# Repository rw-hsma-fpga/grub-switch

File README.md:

# THE GRUB SWITCH&nbsp;&nbsp;   

#### See [*quickstart.pdf*](./quickstart.pdf) for the fastest way to your custom boot configuration.

#### (c) 2019-2023 Ruediger Willenberg

This project enables PC users to select the OS to be booted by *GRUB* through hardware.
It has three independently usable components:

### 1. Configuration scripts ###

A suite of *bash* scripts in **1_config_scripts**, all controlled by one easy-to-use text UI, that provide the following capabilities:
* parse the **grub.cfg** file for all menu entries that represent OS boot options
* enable the user to pick menu entries and order them with numbers (1..15)
* generate *GRUB* script files that make a specific menu entry the default choice; these files can be put on separate USB flash drives; plugging one in will represent that choice of OS to be booted
* enhance the existing **grub.cfg** - in a non-destructive way that survives kernel updates - to look for a boot choice script on a plugged-in drive
* install a list of file hashes in *GRUB* so that only the generated files will be executed

When using several USB flash drives for the boot choices (small, old ones will do), no further hardware is necessary.

*GRUB* does not need to be patched, rebuilt or reinstalled. The employed extension of **grub.cfg** is robust against unavailable or malformed data. Any unexpected choices or scripts will be ignored. You can always get to the regular *GRUB* boot menu.

### 2. USB device firmware

The **2_usb_device** directory holds firmware source code for *Microchip/Atmel ATmega32U4* MCUs that can act as USB devices. It has build support and pre-built firmware images for common maker boards like *Teensy 2.0*, *Arduino Micro*, *Adafruit ItsyBitsy* and *Sparkfun Pro Micro*. Other boards with the ATmega32u4 can be easily added.

A board with the firmware installed will register as a regular USB flash drive when plugged in and provide one of the generated files for the regular flash drives; however, you can control which file (i.e. which boot choice) is picked through pins on the board.

The firmware does NOT need to be rebuilt to change the boot configuration; a new boot configuration can just be written to the USB drive. With a switch or jumper, *write-protect* can be activated.

Boards can be connected to common *rotary*, *toggle* or *binary-encoding* switches to realize boot choice.

### 3. Custom USB Hardware 

For easier panel and case mounting (and for fun), we designed our own PCB for *ATmega32U4* or *ATmega16U4* chips. *EAGLE* and *Gerber* files and all other required information can be found in **3_custom_hardware**. It features:

* Solder pads for common *1-of-12-rotary encoder* and *on/off/on-toggle* switches with front panel mounting threads; no soldering cables required.
* Supports USB connection both by *Mini-B*-plug or directly by internal ribbon cable to motherboard USB pinheaders.
* Firmware easily re-programmable by pushing a button; works with factory *ATmega32U4* chips, no custom bootloader needs to be installed.
* Switch- or jumper-controlled *write-protect*
* Can be used with self-written firmware for other purposes, like any commercial board; provides up to 13 I/O-pins with 5V logic.

Obviously this requires soldering skills and is likely not the cheapest hardware option, especially because you have to order your own PCB. But it's fun!

### NEW: Miscellaneous contributions
In directory *4_misc*, you can find community contributions like case designs and wiring diagrams that could be helpful with GRUB Switch building, mounting, etc.

---

### Acknowledgements 

Many thanks to Seriosha Remmlinger, Volker Wunsch and Andreas Flachsbarth for helpful feedback and suggestions and to Christoph Dehmer for examining an alternative approach (GRUB menu control by USB HID keyboard).

Thank you to Pina Merkert from Germany's biggest computer magazine [*c't*](https://www.heise.de/ct) for helping me write and publish an article about this, and for her cool contributions in *4_misc*.

Stephen Holdaway has a very cool [*Hackaday* project](https://hackaday.io/project/179539-hardware-boot-selection-switch) doing something similar with an *STM32* controller. He's built a very neat way to define the FAT file structure in his C code.

We are grateful to [*pid.codes*](https://pid.codes/) for providing our firmware with a unique USB ID *(VID 1209 / PID 2015)*.

Thank you to the GNU GRUB developers and maintainers for all their hard work.

---

#### See [*quickstart.pdf*](./quickstart.pdf) for the fastest way to your custom boot configuration.

The [*documentation*](./documentation/) directory holds more detailed information.

Send any questions or suggestions to [*grubswitch@gmail.com*](mailto:grubswitch@gmail.com). Please be patient. I have a life.

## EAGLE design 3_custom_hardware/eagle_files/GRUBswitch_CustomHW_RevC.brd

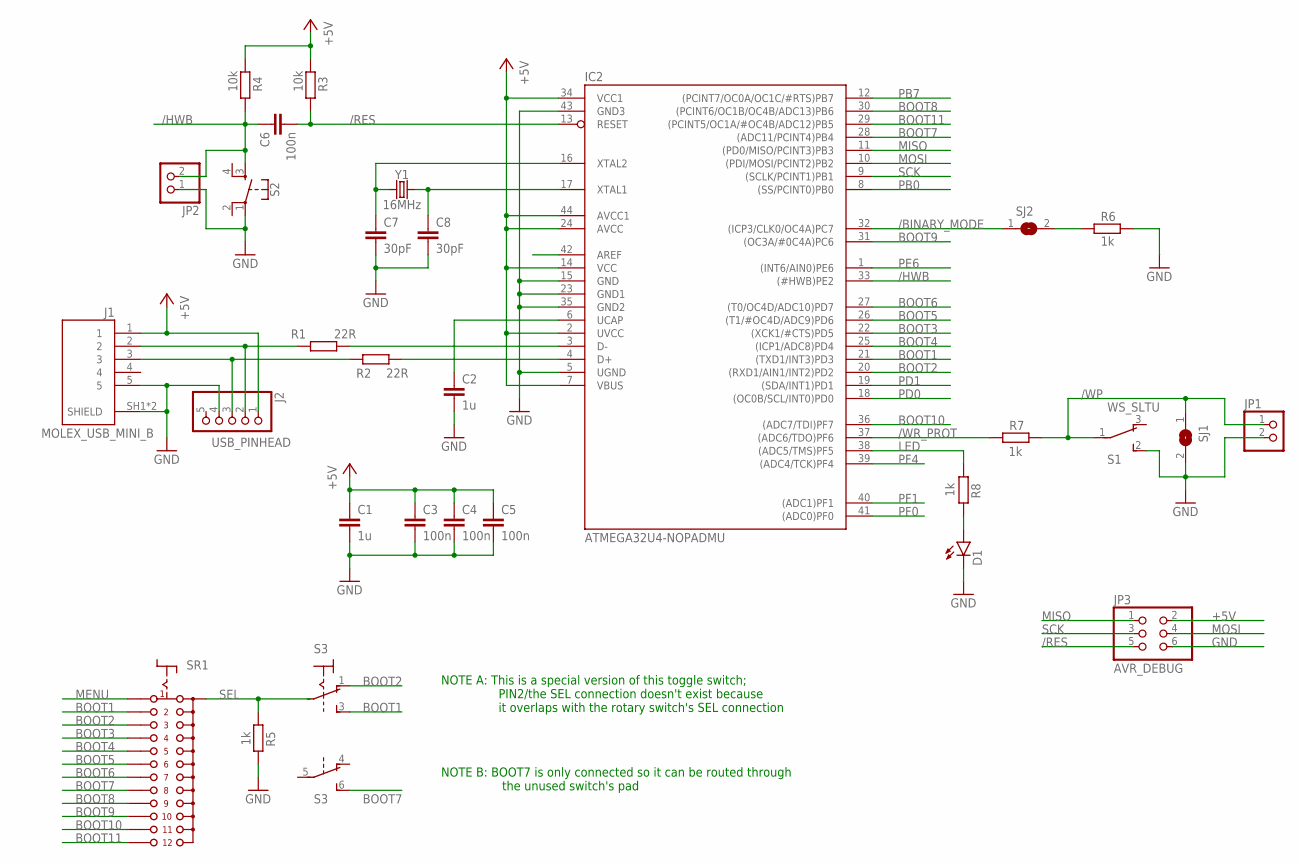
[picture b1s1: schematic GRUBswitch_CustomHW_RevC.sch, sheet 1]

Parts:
C1, C2: 1u; C0805
C3, C4, C5, C6: 100n; C0805
C7, C8: 30pF; C0805
D1: LEDCHIPLED_0805; CHIPLED_0805
IC2: ATMEGA32U4-NOPADMU; QFN-44-NOPAD
J1: MOLEX_USB_MINI_B; MOLEX_502237-0517
J2: USB_PINHEAD; 1X05
JP1, JP2: PINHD-1X2; 1X02
JP3: AVR_DEBUG; 2X03_SMD
R1, R2: 22R; R0805
R3, R4: 10k; R0805
R5, R6, R7, R8: 1k; R0805
S1: WS_SLTU
S2: MOMENTARY-SWITCH-SPST-2-SMD-4.5MM; TACTILE_SWITCH_SMD_4.5MM
S3: M9040P2
SJ1, SJ2: SJ
SR1: CK101X12+
Y1: 16MHz; CRYSTAL-SMD-5X3.2-2PAD

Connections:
+5V: C1.1, C3.1, C4.1, C5.1, IC2.2 (UVCC), IC2.7 (VBUS), IC2.14 (VCC), IC2.24 (AVCC), IC2.34 (VCC1), IC2.44 (AVCC1), J1.1, J2.1, JP3.2, R3.2, R4.2; also elsewhere on the board
/BINARY_MODE: IC2.32 ((ICP3/CLK0/OC4A)PC7), SJ2.1; also elsewhere on the board
/BM: R6.1, SJ2.2
/HWB: C6.1, IC2.33 ((#HWB)PE2), JP2.2, R4.1, S2.3; also elsewhere on the board
/RES: C6.2, IC2.13 (RESET), JP3.5, R3.1; also elsewhere on the board
/WP: JP1.1, R7.1, S1.1, SJ1.1
/WR_PROT: IC2.37 ((ADC6/TDO)PF6), R7.2; also elsewhere on the board
AREF: IC2.42 (AREF); also elsewhere on the board
BOOT1: IC2.21 ((TXD1/INT3)PD3), S3.3 (S), SR1.2; also elsewhere on the board
BOOT2: IC2.20 ((RXD1/AIN1/INT2)PD2), S3.1 (O), SR1.3; also elsewhere on the board
BOOT3: IC2.22 ((XCK1/#CTS)PD5), SR1.4; also elsewhere on the board
BOOT4: IC2.25 ((ICP1/ADC8)PD4), SR1.5; also elsewhere on the board
BOOT5: IC2.26 ((T1/#OC4D/ADC9)PD6), SR1.6; also elsewhere on the board
BOOT6: IC2.27 ((T0/OC4D/ADC10)PD7), SR1.7; also elsewhere on the board
BOOT7: IC2.28 ((ADC11/PCINT4)PB4), S3.6 (S), SR1.8; also elsewhere on the board
BOOT8: IC2.30 ((PCINT6/OC1B/OC4B/ADC13)PB6), SR1.9; also elsewhere on the board
BOOT9: IC2.31 ((OC3A/#0C4A)PC6), SR1.10; also elsewhere on the board
BOOT10: IC2.36 ((ADC7/TDI)PF7), SR1.11; also elsewhere on the board
BOOT11: IC2.29 ((PCINT5/OC1A/#OC4B/ADC12)PB5), SR1.12; also elsewhere on the board
D+: J1.3, J2.3, R2.1
D-: J1.2, J2.2, R1.1
GND: C1.2, C2.2, C3.2, C4.2, C5.2, C7.2, C8.2, D1.C, IC2.5 (UGND), IC2.15 (GND), IC2.23 (GND1), IC2.35 (GND2), IC2.43 (GND3), J1.5, J1.SH1 (SHIELD), J1.SH2 (SHIELD), J2.4, JP1.2, JP2.1, JP3.6, R5.2, R6.2, S1.2 (S), S2.1, SJ1.2; also elsewhere on the board
LED: IC2.38 ((ADC5/TMS)PF5), R8.2; also elsewhere on the board
MENU: SR1.1
MISO: IC2.11 ((PD0/MISO/PCINT3)PB3), JP3.1; also elsewhere on the board
MOSI: IC2.10 ((PDI/MOSI/PCINT2)PB2), JP3.4; also elsewhere on the board
unnamed: D1.A, R8.1
PB0: IC2.8 ((SS/PCINT0)PB0); also elsewhere on the board
PB7: IC2.12 ((PCINT7/OC0A/OC1C/#RTS)PB7); also elsewhere on the board
PD0: IC2.18 ((OC0B/SCL/INT0)PD0); also elsewhere on the board
PD1: IC2.19 ((SDA/INT1)PD1); also elsewhere on the board
PE6: IC2.1 ((INT6/AIN0)PE6); also elsewhere on the board
PF0: IC2.41 ((ADC0)PF0); also elsewhere on the board
PF1: IC2.40 ((ADC1)PF1); also elsewhere on the board
PF4: IC2.39 ((ADC4/TCK)PF4); also elsewhere on the board
R_D+: IC2.4 (D+), R2.2; also elsewhere on the board
R_D-: IC2.3 (D-), R1.2; also elsewhere on the board
SCK: IC2.9 ((SCLK/PCINT1)PB1), JP3.3; also elsewhere on the board
SEL: R5.1, SR1.A
UCAP: C2.1, IC2.6 (UCAP); also elsewhere on the board
XTAL1: C8.1, IC2.17 (XTAL1), Y1.P$2 (2); also elsewhere on the board
XTAL2: C7.1, IC2.16 (XTAL2), Y1.P$1 (1); also elsewhere on the board

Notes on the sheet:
NOTE A: This is a special version of this toggle switch; PIN2/the SEL connection doesn't exist because it overlaps with the rotary switch's SEL connection
NOTE B: BOOT7 is only connected so it can be routed through the unused switch's pad

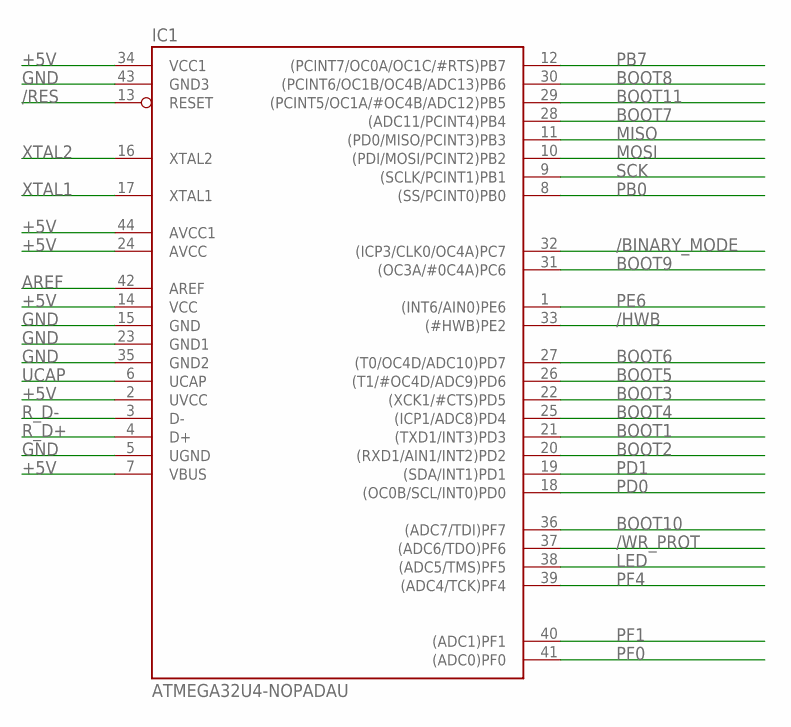
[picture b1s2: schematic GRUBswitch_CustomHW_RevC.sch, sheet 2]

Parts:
IC1: ATMEGA32U4-NOPADAU; TQFP44

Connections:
+5V: IC1.2 (UVCC), IC1.7 (VBUS), IC1.14 (VCC), IC1.24 (AVCC), IC1.34 (VCC1), IC1.44 (AVCC1); also elsewhere on the board
/BINARY_MODE: IC1.32 ((ICP3/CLK0/OC4A)PC7); also elsewhere on the board
/HWB: IC1.33 ((#HWB)PE2); also elsewhere on the board
/RES: IC1.13 (RESET); also elsewhere on the board
/WR_PROT: IC1.37 ((ADC6/TDO)PF6); also elsewhere on the board
AREF: IC1.42 (AREF); also elsewhere on the board
BOOT1: IC1.21 ((TXD1/INT3)PD3); also elsewhere on the board
BOOT2: IC1.20 ((RXD1/AIN1/INT2)PD2); also elsewhere on the board
BOOT3: IC1.22 ((XCK1/#CTS)PD5); also elsewhere on the board
BOOT4: IC1.25 ((ICP1/ADC8)PD4); also elsewhere on the board
BOOT5: IC1.26 ((T1/#OC4D/ADC9)PD6); also elsewhere on the board
BOOT6: IC1.27 ((T0/OC4D/ADC10)PD7); also elsewhere on the board
BOOT7: IC1.28 ((ADC11/PCINT4)PB4); also elsewhere on the board
BOOT8: IC1.30 ((PCINT6/OC1B/OC4B/ADC13)PB6); also elsewhere on the board
BOOT9: IC1.31 ((OC3A/#0C4A)PC6); also elsewhere on the board
BOOT10: IC1.36 ((ADC7/TDI)PF7); also elsewhere on the board
BOOT11: IC1.29 ((PCINT5/OC1A/#OC4B/ADC12)PB5); also elsewhere on the board
GND: IC1.5 (UGND), IC1.15 (GND), IC1.23 (GND1), IC1.35 (GND2), IC1.43 (GND3); also elsewhere on the board
LED: IC1.38 ((ADC5/TMS)PF5); also elsewhere on the board
MISO: IC1.11 ((PD0/MISO/PCINT3)PB3); also elsewhere on the board
MOSI: IC1.10 ((PDI/MOSI/PCINT2)PB2); also elsewhere on the board
PB0: IC1.8 ((SS/PCINT0)PB0); also elsewhere on the board
PB7: IC1.12 ((PCINT7/OC0A/OC1C/#RTS)PB7); also elsewhere on the board
PD0: IC1.18 ((OC0B/SCL/INT0)PD0); also elsewhere on the board
PD1: IC1.19 ((SDA/INT1)PD1); also elsewhere on the board
PE6: IC1.1 ((INT6/AIN0)PE6); also elsewhere on the board
PF0: IC1.41 ((ADC0)PF0); also elsewhere on the board
PF1: IC1.40 ((ADC1)PF1); also elsewhere on the board
PF4: IC1.39 ((ADC4/TCK)PF4); also elsewhere on the board
R_D+: IC1.4 (D+); also elsewhere on the board
R_D-: IC1.3 (D-); also elsewhere on the board
SCK: IC1.9 ((SCLK/PCINT1)PB1); also elsewhere on the board
UCAP: IC1.6 (UCAP); also elsewhere on the board
XTAL1: IC1.17 (XTAL1); also elsewhere on the board
XTAL2: IC1.16 (XTAL2); also elsewhere on the board

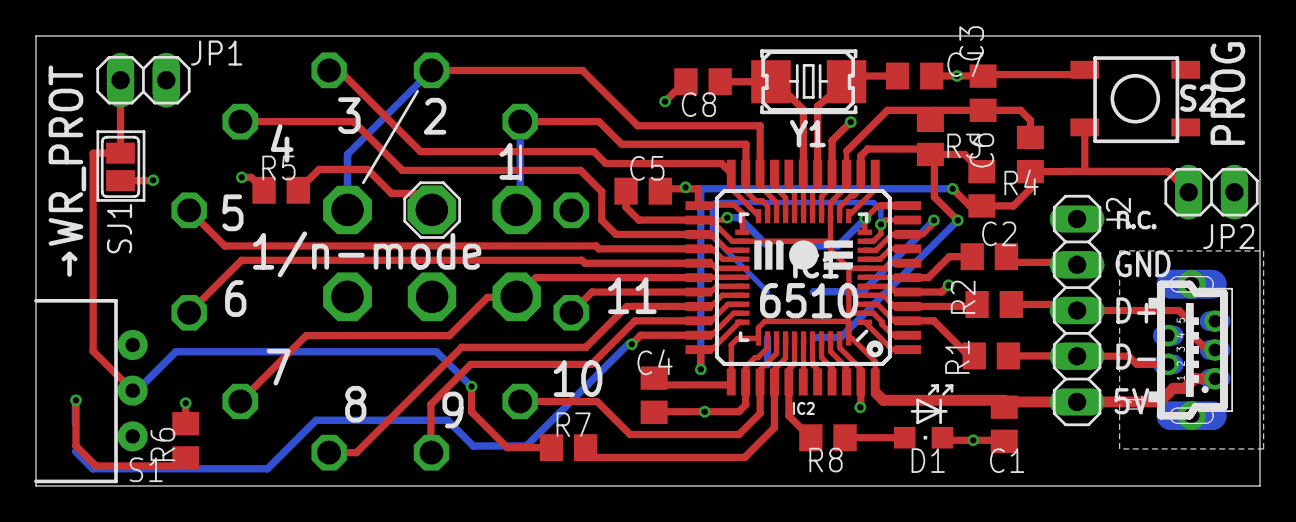
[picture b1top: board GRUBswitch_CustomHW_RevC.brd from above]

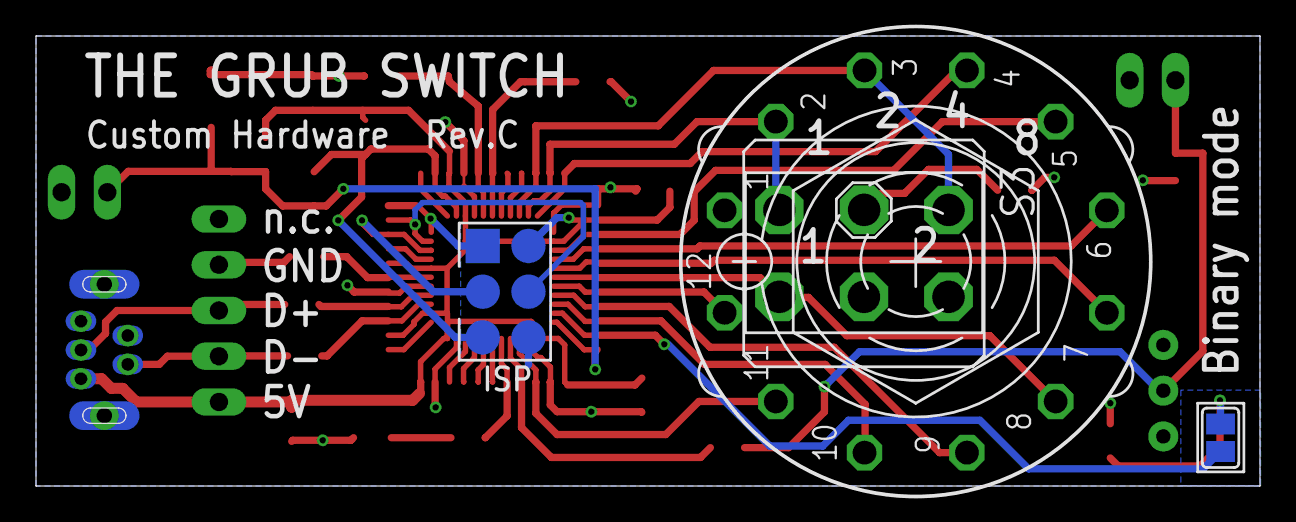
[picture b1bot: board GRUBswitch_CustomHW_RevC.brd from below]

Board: 2 copper layers, 68.0 x 25.0 mm, 31 parts (4 on the bottom side), 41 nets.

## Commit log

2019-07-31 First commit; usb_device firmware working on Teensy 2.0
2019-07-31 README.md fix; added grub-switch-configure dir
2019-08-05 Added Linux shell script folder, first empty script
2019-08-05 Added second empty shell script
2019-08-05 Menuentry extraction script working
2019-08-06 Script for copying menuentry file to GRUB Switch working
2019-08-17 First versions of scripts for making bootfiles, modifying grub.cfg through update-grub
2019-08-20 Extended grub.cfg parsing script to generate submenu entries: submenu1>submenu2>menuentry
2019-08-20 Modified .gitignore to ignore generated hashes
2020-09-17 new development branch for menu shell script
2020-09-17 modifications to menutest_dev branch
2020-10-02 Cleaned up board-specific headers; added WR_PROT pin and corresponding write-protect functionality; added Custom HW Grub Switch board
2020-10-26 Changed PID to 2015 (pid.codes); fixed bootpins.ini generation
2020-10-26 Shutting off JTAG so Port F can be used for I/O
2020-10-29 Added ESC to menu to SWITCH.GRB ; added auxiliary low-pin
2020-11-10 Added AUX0 pins, added multiple boards
2020-11-12 Include /WRPROT,/BM in change detection
2020-11-15 Fixed reattach for all pin changes; various board file modifications
2020-11-15 Bootscript change: ESC stops boot but keeps choice.
2020-12-27 Added parsing for individual colors and times in entries files
2020-12-27 shell scripts adjustments for individual entry colors/times
2021-01-13 Added Custom HW Rev.B target
2021-05-08 Added Master config script; unfinished
2021-05-08 Added Master config script; still unfinished
2021-05-11 script rebuild, continuing.
2021-05-11 Added remove_grubswitch script
2021-05-12 added hash install/remove scripts
2021-05-12 Renamed shells script folder
2021-05-12 Renamed usb device folder
2021-05-12 cleanup
2021-05-12 added move_to_USB script (unfinished)
2021-05-13 Update README, LICENSE
2021-05-13 all sub-scripts included and working
2021-05-13 Fixed bug in .entries.txt generation
2021-05-21 Added DFR Beetle, programming scripts for arduino and DFU
2021-05-21 sync fix 1
2021-05-21 DFR sync fix 2
2021-05-23 First version of quickstart documentation
2021-05-24 added wiring info to quickstart.pdf
2021-05-24 Fixed quickstart.pdf link
2021-05-24 Fixed quickstart.pdf link, removed README backup
2021-05-25 tag/release test commit
2021-05-25 Updated quickstart.pdf
2021-05-28 Extended board documentation, minor script fixes
2021-06-14 Started USB device documentation; custom HW BOM enhanced
2021-06-15 2_usb_device documentation completed
2021-06-15 Started custom hardware documentation
2021-06-15 Finished custom hardware documentation, fixed minor bugs in other documentation
2021-06-16 Started 1_config_scripts documentation
2021-06-17 Changed comments in generated files, added GeneralInfo doc
2021-06-19 Documentation finished (for now...)
2021-06-20 made bootfile strings and bootbins.txt labels const code/PROGMEM
2021-06-20 SWITCH.GRB parameters assembled from ROM when read, no SRAM buffer
2021-06-20 Code cleanup after SRAM use optimization
2021-06-20 Added Custom HW support for ATmega16u4 b/c of chip shortage
2022-06-21 Cleaned leftover disassembly
2022-06-21 Removed debug artifacts
2022-06-21 Removed CR from generated SWITCH.GRB; was inconsistent with individual bootfiles and hashes
2022-06-21 Extended DFU script for ATmega16u4 (no make option yet)
2022-06-21 Updated prebuilt binaries to current code base
2022-06-22 DFU script with support for both dfu-programmer 0.6.x and 0.7.x
2022-06-22 Added prebuilt-copy to Makefile; shortened build prefix to GS_
2022-06-22 Added atmega16u4 compile for Custom Hardware Rev.B
2022-06-23 Added Custom HW Revision C firmware; board documentation to be added
2022-06-23 Title image in README
2022-06-23 License badge
2022-06-23 Maintainer and email badge
2022-06-23 email badge with mailto link
2022-06-23 Linebreak badge fix, email colour
2022-06-27 Updated CustomHW Rev.B BOM with ATmega16U4
2022-06-27 Added ATmega16U4 and dfu-programmer 0.6.x info to text info
2022-06-27 Shortened hex file prefix to GS_ in text info files
2022-06-27 Added ATmega16U4 and dfu-programmer 0.6.x to 2_usb_device documentation
2022-06-27 Added /HWB fix, ATmega16U4 and dfu-programmer 0.6.x to 3_custom_hardware documentation
2022-06-27 Moved Custom HW RevB files into legacy folder
2022-06-27 Moved RevB src images, add RevC ones
2022-06-27 Updated RevC BOM with MU variants
2022-06-27 Updated 2_usb_device documentation for Custom HW RevC and 16u4 variants
2022-06-27 Updated 3_custom_hardware documentation for Custom HW Rev.C
2022-06-27 Updated Quickstart documentation for Custom HW Rev.C
2022-06-27 Fixed HEX image GS_ prefixes in documentation files
2022-06-27 Updated README.md with 16u4 and link to Stephen H.'s project
2022-06-28 Added GRUB 2.06 changes to documentation
2022-08-04 Fixed chosen entries display
2022-08-04 Modified terminal color warning
2022-08-05 Last switch configuration is read and used
2022-08-05 Last configuration time and colors used
2022-08-14 Added 'Clear all by Backspace' to configuration
2023-01-11 Fixed typo in README.md
2023-03-11 grub.cfg parser fixed to work with quotes and apostrophes; thanks for the heads-up Maxime G (joihn)
2023-04-12 Fixed wrapper call for grub2-mkconfig
2023-04-12 Redirecting stderr when calling tool which
2023-04-16 Changed default OS choice display time from 000 to 003
2023-04-16 Asking for sudo if grub.cfg status requires it
2023-04-16 Removed sudo status from status display; takes space and not much use
2023-04-16 Added check for required command line tools
2023-04-17 Updated README copyright date
2023-04-19 sudo which to find more tool paths
2023-04-21 reworked sudo usage; minor output corrections
2023-04-21 moved update-grub search and call into helper functions
2023-04-21 Added optional update-grub before menu extraction
2023-04-22 Added command-line parameter and checking for Boot Loader Specification path (Fedora etc.)
2023-04-22 Added menu entry extraction from BLS conf files (Fedora)
2023-04-22 Set minimum of 2 choice display seconds for breakoff reasons
2023-04-22 Force no-timeout GRUB Menu on mismatched hashes
2023-04-22 Fixed README title image
2023-04-22 Added hash generation for empty SWITCH.GRB file
2023-04-28 Removed inconsistent sudo markers in Action menu
2023-04-29 Updated documentation 0_General_Information with current data
2023-04-30 Updated Quickstart documentation and related screenshots
2023-04-30 Updated documentation about config scripts
2023-04-30 Updated and renamed GRUB2.06 info file
2023-05-13 Added Arduino Leonardo to boards
2023-05-13 Added 4_misc/ with community contributions
2024-02-18 Update folder names in gitignore

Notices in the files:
README.md:
License: MIT
